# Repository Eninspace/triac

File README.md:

This project is based on esp8266 and TRIAC for control power via remote control.

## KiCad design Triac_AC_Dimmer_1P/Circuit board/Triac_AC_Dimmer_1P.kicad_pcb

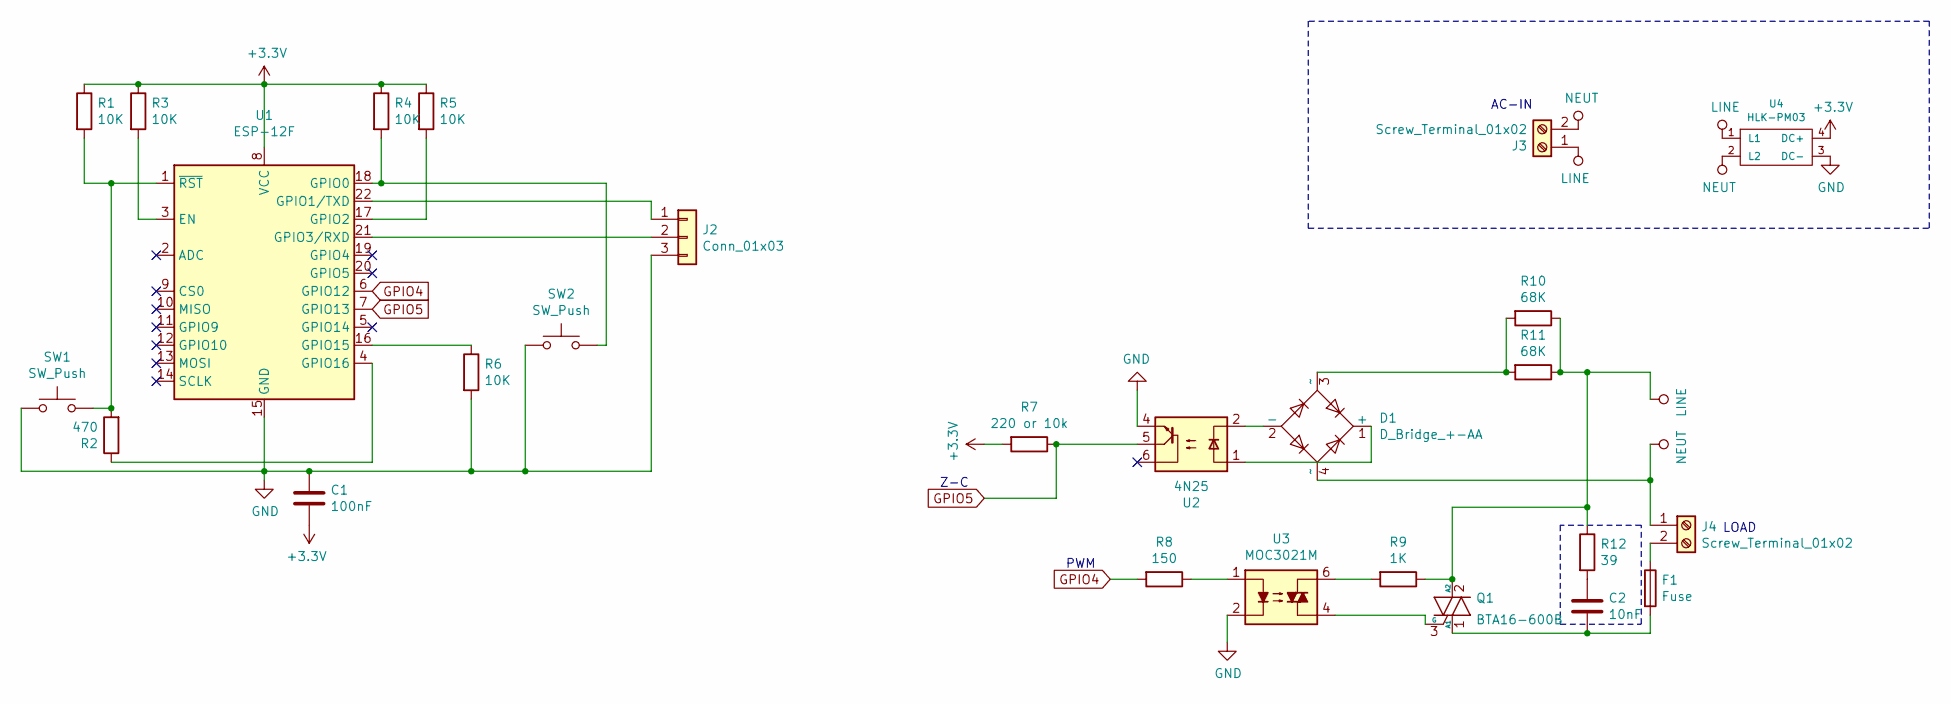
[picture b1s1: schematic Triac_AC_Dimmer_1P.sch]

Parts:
C1: 100nF; C_0805_2012Metric
C2: 10nF; C_Rect_L13.0mm_W5.0mm_P10.00mm_FKS3_FKP3_MKS4
D1: D_Bridge_+-AA; Diode_Bridge_Diotec_SO-DIL-Slim
F1: Fuse; Fuseholder_Blade_Mini_Keystone_3568
J2: Conn_01x03; PinHeader_1x03_P2.54mm_Vertical
J3, J4: Screw_Terminal_01x02; TerminalBlock_bornier-2_P5.08mm
Q1: BTA16-600B; TO-220-3_Vertical
R1, R3, R4, R5, R6: 10K; R_1206_3216Metric
R2: 470; R_1206_3216Metric
R7: 220 or 10k; R_1206_3216Metric
R8: 150; R_1206_3216Metric
R9: 1K; R_Axial_DIN0516_L15.5mm_D5.0mm_P5.08mm_Vertical
R10, R11: 68K; R_Axial_DIN0516_L15.5mm_D5.0mm_P5.08mm_Vertical
R12: 39; R_Axial_DIN0516_L15.5mm_D5.0mm_P5.08mm_Vertical
SW1, SW2: SW_Push; SW_SPST_CK_RS282G05A3
U1: ESP-12F; ESP-12E
U2: 4N25; DIP-6_W7.62mm
U3: MOC3021M; DIP-6_W7.62mm
U4: HLK-PM03

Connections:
+3V3: C1.2, R1.1, R3.1, R4.1, R5.1, R7.2, U1.8 (VCC), U4.4 (DC+)
GND: C1.1, J2.3, R6.2, SW1.1, SW2.1, U1.15 (GND), U2.4, U3.2, U4.3 (DC-)
GPIO4: R8.2, U1.6 (GPIO12)
GPIO5: R7.1, U1.7 (GPIO13), U2.5
LINE: J3.1, Q1.2 (A2), R9.1, R10.1, R11.1, R12.1, U4.1 (L1)
NEUT: D1.4 (~~), J3.2, J4.1, U4.2 (L2)
unnamed: C2.1, R12.2
unnamed: C2.2, F1.2, Q1.1 (A1)
unnamed: D1.1 (+), U2.1
unnamed: D1.2 (-), U2.2
unnamed: D1.3 (~~), R10.2, R11.2
unnamed: F1.1, J4.2
unnamed: J2.1, U1.22 (GPIO1/TXD)
unnamed: J2.2, U1.21 (GPIO3/RXD)
unnamed: Q1.3 (G), U3.4
unnamed: R1.2, R2.2, SW1.2, U1.1 (~RST)
unnamed: R2.1, U1.4 (GPIO16)
unnamed: R3.2, U1.3 (EN)
unnamed: R4.2, SW2.2, U1.18 (GPIO0)
unnamed: R5.2, U1.17 (GPIO2)
unnamed: R6.1, U1.16 (GPIO15)
unnamed: R8.1, U3.1
unnamed: R9.2, U3.6

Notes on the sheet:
AC-IN
LOAD
PWM
Z-C

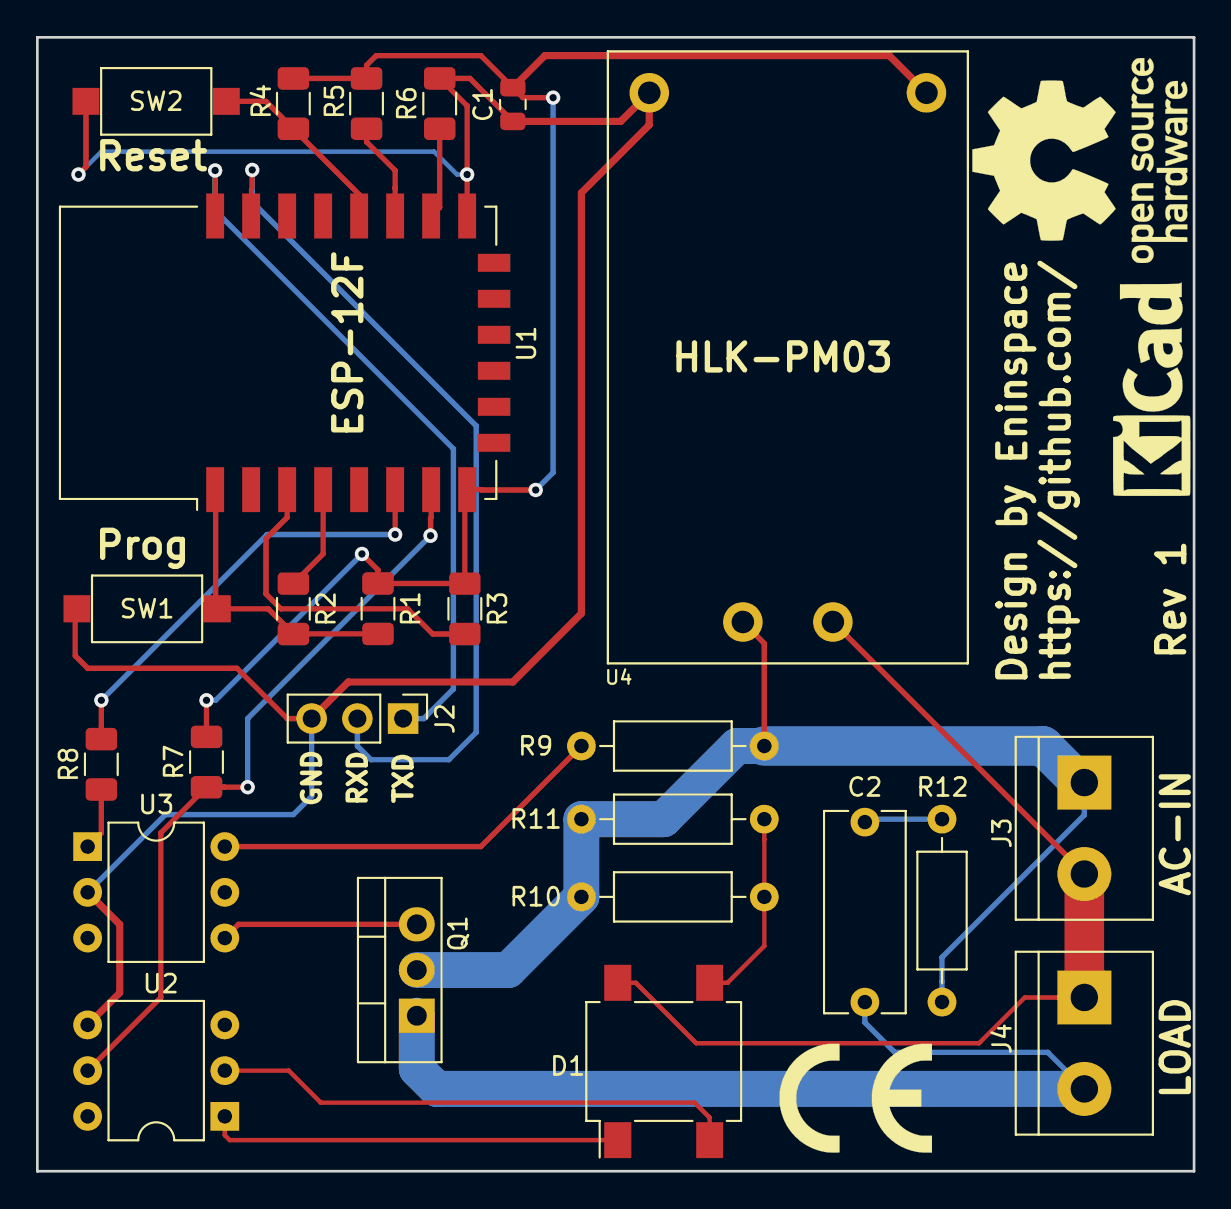
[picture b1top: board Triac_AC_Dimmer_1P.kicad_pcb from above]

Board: 2 copper layers, 64.3 x 63.0 mm, 25 parts (0 on the bottom side), 22 nets.

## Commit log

2018-12-22 Create 1
2018-12-22 Create test
2018-12-22 Update test
2018-12-22 Rename test to prog_dimming
2018-12-22 Create test_dimmer
2018-12-22 Rename prog_dimming to prog_dimming.ino
2018-12-22 Rename test_dimmer to test_dimmer.ino
2019-01-12 Update Triac
    Changed the seats for some capacitors and resistors
2019-04-28 Creadte and update main_dimmer
